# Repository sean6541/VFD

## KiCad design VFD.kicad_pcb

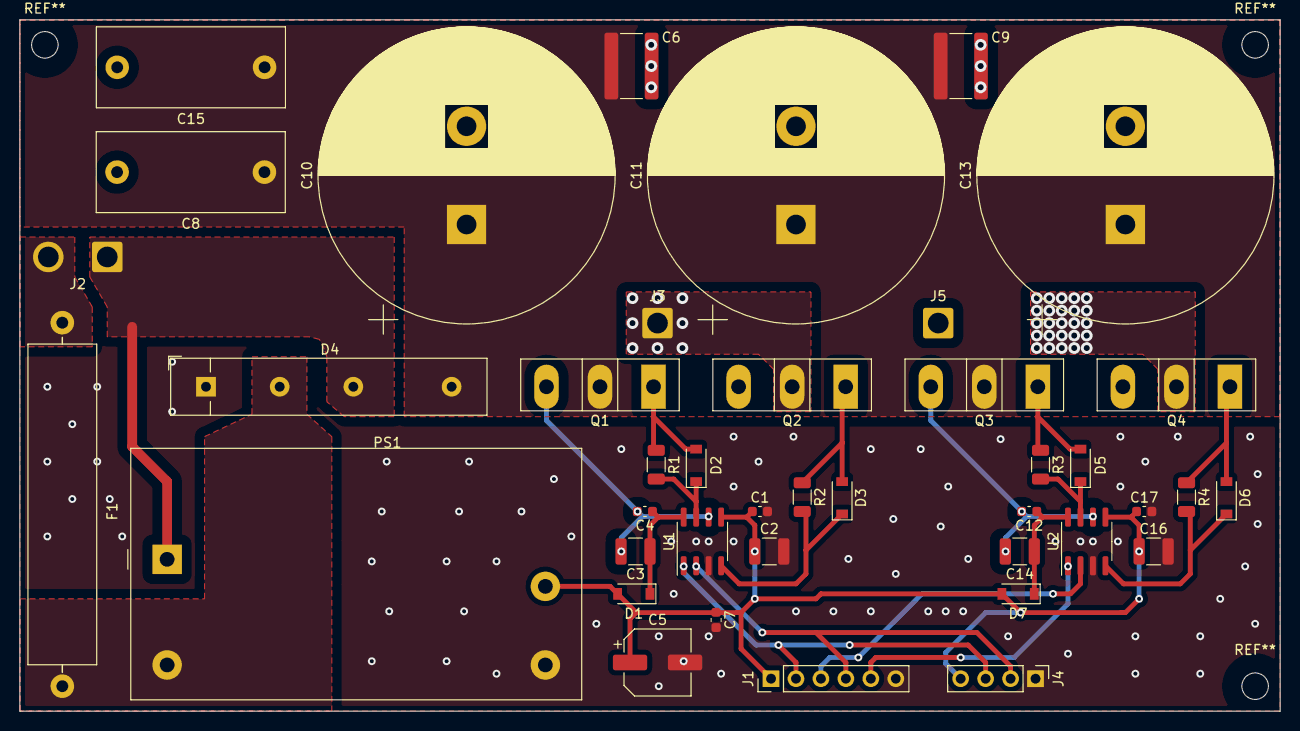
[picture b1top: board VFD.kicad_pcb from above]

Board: 2 copper layers, 128.3 x 70.4 mm, 41 parts (0 on the bottom side), 22 nets.

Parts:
C1, C4, C7, C12, C17: 0.1u; C_0603_1608Metric
C2, C3, C14, C16: 10u; C_1210_3225Metric
C5: 100u; CP_Elec_6.3x5.4
C6, C9: 0.1u; C_1825_4564Metric
C8, C15: 1u; C_Rect_L19.0mm_W8.0mm_P15.00mm_MKS4
C10, C11, C13: 2200u; CP_Radial_D30.0mm_P10.00mm_SnapIn
D1, D2, D3, D5, D6, D7: D; D_SOD-123
D4: D_Bridge_-AA+; Diode_Bridge_32.0x5.6x17.0mm_P10.0mm_P7.5mm
F1: 15; Fuse_SunFuse-6HP
J1: Conn_01x06; PinHeader_1x06_P2.54mm_Vertical
J2: Screw_Terminal_01x02; SolderWire-1.5sqmm_1x02_P6mm_D1.7mm_OD3mm
J3, J5: Screw_Terminal_01x01; SolderWire-1.5sqmm_1x01_D1.7mm_OD3mm
J4: Conn_01x04; PinHeader_1x04_P2.54mm_Vertical
PS1: IRM-05-12; Converter_ACDC_MeanWell_IRM-05-xx_THT
Q1, Q2, Q3, Q4: IPW60R037CSFD; TO-247-3_Vertical
R1, R2, R3, R4: 10; R_1206_3216Metric
U1, U2: 2ED2182S06F; SOIC-8_3.9x4.9mm_P1.27mm

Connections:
+12V: C1.1, C2.1, C5.1, C7.1, C16.1, C17.1, D1.2, D7.2, J1.1, J4.4, PS1.4, U1.5, U2.5
DRV_A: J1.2, J4.3, U1.1
DRV_B: J1.4, J4.2, U1.2
DRV_C: J1.5, U2.1
DRV_D: J1.3, U2.2
GND: C1.2, C2.2, C5.2, C6.2, C7.2, C8.2, C9.2, C10.2, C11.2, C13.2, C15.2, C16.2, C17.2, D4.1, J1.6, J4.1, PS1.3, Q2.3, Q4.3, U1.3, U2.3
LINE: F1.2, J2.2
NEUT: D4.3, J2.1, PS1.1
unnamed: C3.1, C4.1, D1.1, U1.8
unnamed: C12.1, C14.1, D7.1, U2.8
unnamed: D2.1, R1.2, U1.7
unnamed: D2.2, Q1.1, R1.1
unnamed: D3.1, R2.2, U1.4
unnamed: D3.2, Q2.1, R2.1
unnamed: D4.2, F1.1, PS1.2
unnamed: D5.1, R3.2, U2.7
unnamed: D5.2, Q3.1, R3.1
unnamed: D6.1, R4.2, U2.4
unnamed: D6.2, Q4.1, R4.1
VCC: C6.1, C8.1, C9.1, C10.1, C11.1, C13.1, C15.1, D4.4, Q1.2, Q3.2
VOUT_A: C3.2, C4.2, J3.1, Q1.3, Q2.2, U1.6
VOUT_B: C12.2, C14.2, J5.1, Q3.3, Q4.2, U2.6

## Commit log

2021-03-08 Update Gate Resistor Values
2021-03-19 Fix Issues
